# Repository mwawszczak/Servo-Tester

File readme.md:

# RC Servo Tester — STM32G030K8Tx

A hand-held tester for RC hobby servos, and my first solo PCB project. The goal was to go through the whole process — schematic, PCB layout, SMD soldering, and firmware — from scratch, using KiCad and a bare-metal STM32 build.

## What it does

The tester lets you drive a servo manually or run it through a few automatic routines, without needing a full RC receiver/transmitter setup.

- **Manual mode** — a potentiometer sets the servo position live
- **Auto mode** — cycles through center, min, max, and a continuous sweep between the limits
- A mode switch toggles between manual and auto, a button steps through the auto sub-modes, and a start/stop button arms or disarms the PWM output
- Two LEDs show the current mode and whether the output is armed, through different blink patterns

## Hardware

The board is built around an STM32G030K8Tx, powered from micro USB through an AMS1117 3.3V regulator. It reads the potentiometer on an ADC input, generates the servo PWM signal (50Hz, 1–2ms pulse) from a hardware timer, and has three buttons with on-board RC filtering for hardware debounce. Programming and debugging go through a standard 4-pin SWD header. The design was kept deliberately simple — no protection circuitry beyond the basics — to keep the focus on finishing a working first revision rather than maximizing features.

## Firmware

Bare-metal C on the STM32 HAL, no RTOS. The firmware is split into small, self-contained modules — a mode state machine, button handling, an LED blink engine, potentiometer reading, and servo PWM control — each exposing a small public interface and keeping its internal state private. The main loop polls the buttons, feeds events into the state machine, updates the servo output and LEDs based on the current mode, and repeats — all non-blocking, driven off the system tick.

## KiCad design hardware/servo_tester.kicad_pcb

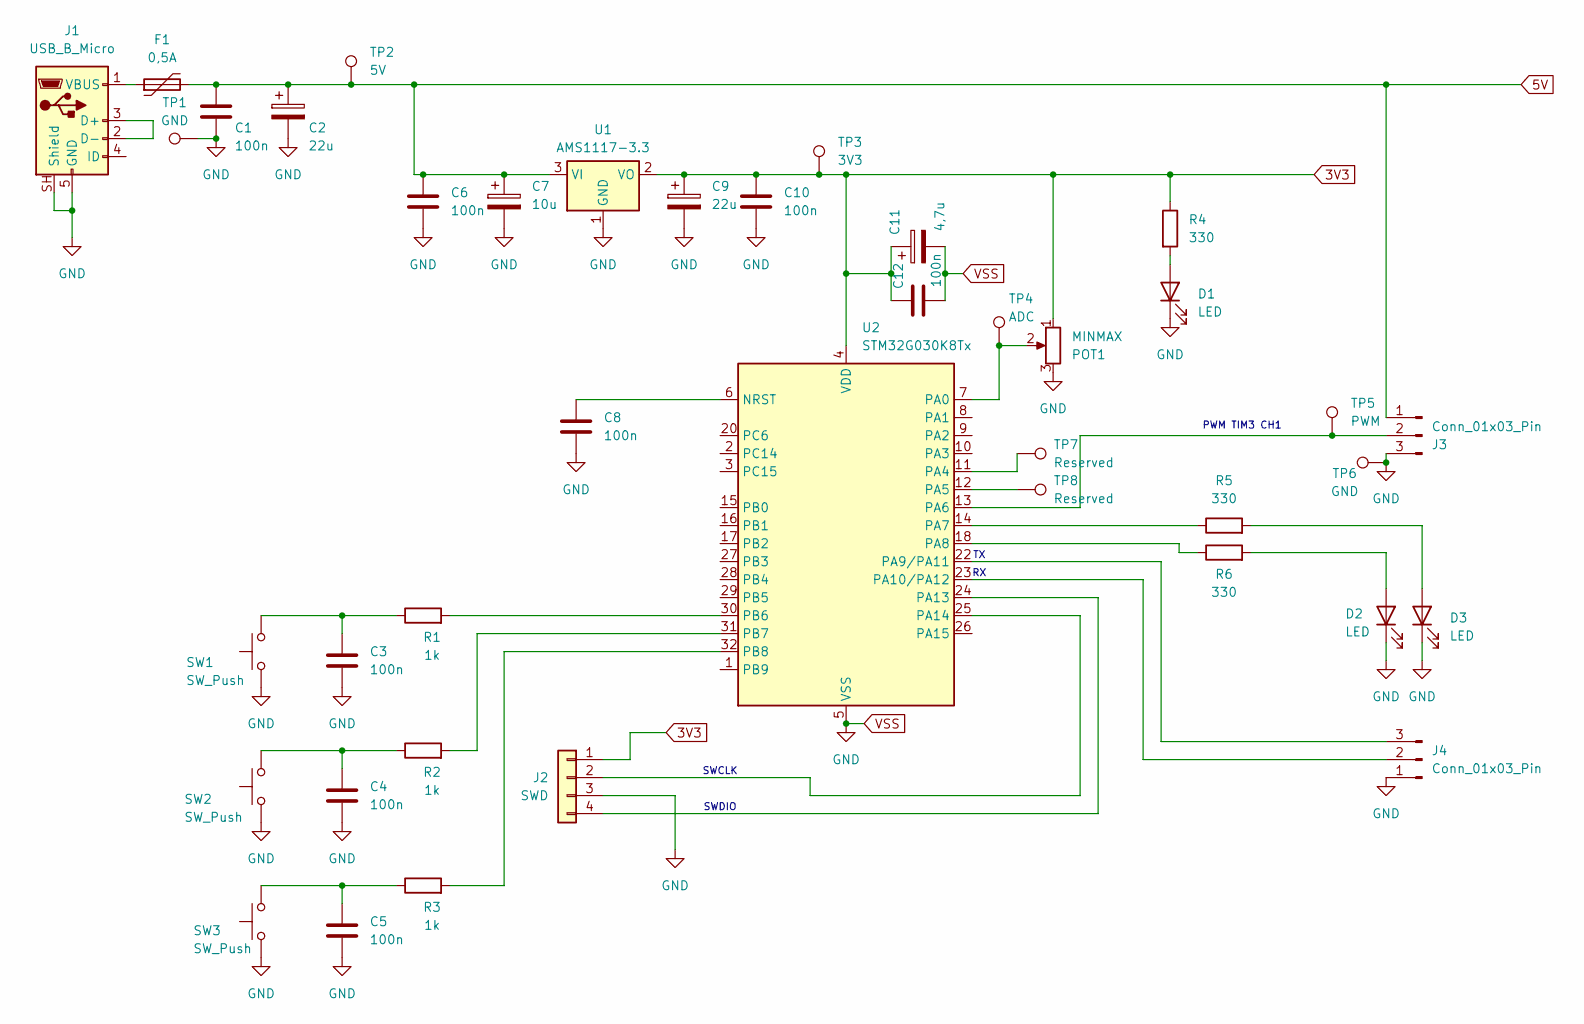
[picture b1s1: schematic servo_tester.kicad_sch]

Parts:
C1, C3, C4, C5, C6, C8, C10, C12: 100n; C_0603_1608Metric_Pad1.08x0.95mm_HandSolder
C2, C9: 22u; CP_Radial_D4.0mm_P1.50mm
C7: 10u; CP_Radial_D4.0mm_P1.50mm
C11: 4,7u; CP_Radial_D4.0mm_P1.50mm
D1, D2, D3: LED; D_1206_3216Metric_Pad1.42x1.75mm_HandSolder
F1: 0,5A; Fuse_1206_3216Metric_Pad1.42x1.75mm_HandSolder
J1: USB_B_Micro; USB_Micro-AB_Molex_47590-0001
J2: SWD; PinHeader_1x04_P2.54mm_Vertical
J3, J4: Conn_01x03_Pin; PinHeader_1x03_P2.54mm_Vertical
POT1: MINMAX; Potentiometer_Alps_RK163_Single_Horizontal
R1, R2, R3: 1k; R_0603_1608Metric_Pad0.98x0.95mm_HandSolder
R4, R5, R6: 330; R_0603_1608Metric_Pad0.98x0.95mm_HandSolder
SW1, SW2, SW3: SW_Push; SW_Push_1P1T_NO_E-Switch_TL3301NxxxxxG
TP1, TP6: GND; TestPoint_THTPad_D1.5mm_Drill0.7mm
TP2: 5V; TestPoint_THTPad_D1.5mm_Drill0.7mm
TP3: 3V3; TestPoint_THTPad_D1.5mm_Drill0.7mm
TP4: ADC; TestPoint_THTPad_D1.5mm_Drill0.7mm
TP5: PWM; TestPoint_THTPad_D1.5mm_Drill0.7mm
TP7, TP8: Reserved; TestPoint_Pad_D1.0mm
U1: AMS1117-3.3; SOT-223-3_TabPin2
U2: STM32G030K8Tx; LQFP-32_7x7mm_P0.8mm

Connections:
3V3: C9.1, C10.1, C11.1, C12.1, J2.1, POT1.1, R4.1, TP3.1 (1_1), U1.2 (VO), U2.4 (VDD)
5V: C1.1, C2.1, C6.1, C7.1, F1.2, J3.1, TP2.1 (1_1), U1.3 (VI)
unnamed: C3.1, R1.1, SW1.2
unnamed: C4.1, R2.1, SW2.2
unnamed: C5.1, R3.1, SW3.2
unnamed: D1.2 (A), R4.2
unnamed: D2.2 (A), R6.2
unnamed: D3.2 (A), R5.2
unnamed: J1.2 (D-), J1.3 (D+)
unnamed: F1.1, J1.1 (VBUS)
unnamed: J2.2, U2.25 (PA14)
unnamed: J2.4, U2.24 (PA13)
unnamed: J3.2, TP5.1 (1_1), U2.13 (PA6)
unnamed: J4.2, U2.23 (PA10/PA12)
unnamed: J4.3, U2.22 (PA9/PA11)
unnamed: C8.1, U2.6 (NRST)
unnamed: POT1.2, TP4.1 (1_1), U2.7 (PA0)
unnamed: TP7.1 (1_1), U2.11 (PA4)
unnamed: TP8.1 (1_1), U2.12 (PA5)
unnamed: R5.1, U2.14 (PA7)
unnamed: R6.1, U2.18 (PA8)
unnamed: R1.2, U2.30 (PB6)
unnamed: R2.2, U2.31 (PB7)
unnamed: R3.2, U2.32 (PB8)
VSS: C1.2, C2.2, C3.2, C4.2, C5.2, C6.2, C7.2, C8.2, C9.2, C10.2, C11.2, C12.2, D1.1 (K), D2.1 (K), D3.1 (K), J1.5 (GND), J1.SH (Shield), J2.3, J3.3, J4.1, POT1.3, SW1.1, SW2.1, SW3.1, TP1.1 (1_1), TP6.1 (1_1), U1.1 (GND), U2.5 (VSS)

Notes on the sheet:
SWCLK
SWDIO
PWM TIM3 CH1

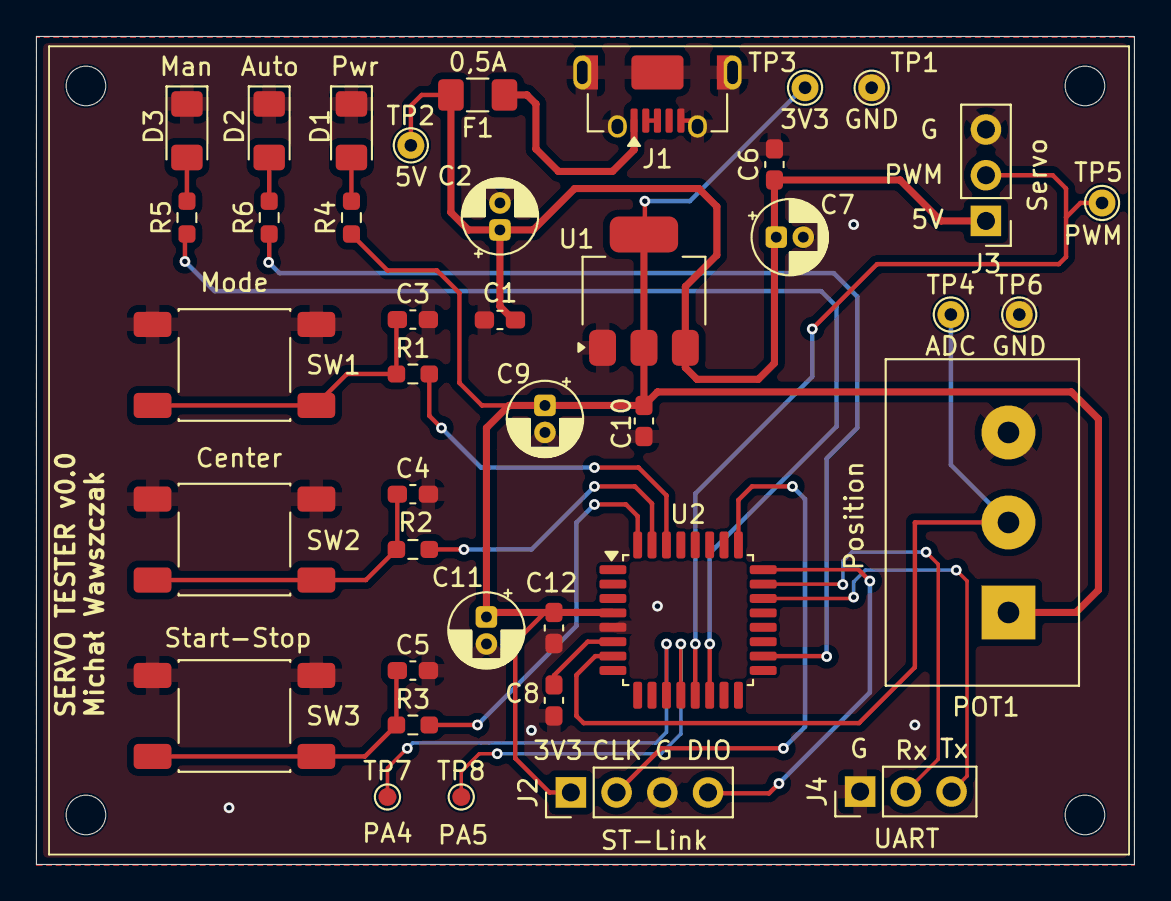
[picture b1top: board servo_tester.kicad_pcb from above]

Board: 2 copper layers, 61.0 x 46.0 mm, 40 parts (0 on the bottom side), 25 nets.

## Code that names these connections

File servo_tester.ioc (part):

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Mcu.Name=STM32G030K(6-8)Tx
Mcu.Package=LQFP32
Mcu.UserName=STM32G030K8Tx
PA0.Mode=IN0
PA0.Signal=ADC1_IN0
PA10.Mode=Asynchronous
PA10.Signal=USART1_RX
PA13.Mode=Serial_Wire
PA13.Signal=SYS_SWDIO
PA14-BOOT0.Mode=Serial_Wire
PA14-BOOT0.Signal=SYS_SWCLK
PA6.Signal=S_TIM3_CH1
PA7.GPIOParameters=GPIO_Label
PA7.GPIO_Label=LED_MODE_MANUAL
PA7.Signal=GPIO_Output
PA8.GPIOParameters=GPIO_Label
PA8.GPIO_Label=LED_MODE_AUTO
PA8.Signal=GPIO_Output
PA9.Mode=Asynchronous
PA9.Signal=USART1_TX
PB6.GPIOParameters=GPIO_PuPd,GPIO_Label
PB6.GPIO_Label=SW_MODE
PB6.GPIO_PuPd=GPIO_PULLUP
PB6.Signal=GPIO_Input
PB7.GPIOParameters=GPIO_PuPd,GPIO_Label
PB7.GPIO_Label=SW_CENTER
PB7.GPIO_PuPd=GPIO_PULLUP
PB7.Signal=GPIO_Input
PB8.GPIOParameters=GPIO_PuPd,GPIO_Label
PB8.GPIO_Label=SW_ARM
PB8.GPIO_PuPd=GPIO_PULLUP
PB8.Signal=GPIO_Input
RCC.HSE_VALUE=8000000
RCC.SYSCLKFreq_VALUE=16000000
board=custom
